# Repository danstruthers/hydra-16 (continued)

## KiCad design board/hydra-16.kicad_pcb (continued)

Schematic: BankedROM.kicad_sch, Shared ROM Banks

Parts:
C38, C39, C40, C41, C42, C43, C44, C45: 104; C_Disc_D5.0mm_W2.5mm_P5.00mm
U30, U31, U32, U33, U34, U35, U36, U37: SST39SF040; DIP-32_W15.24mm_Socket_LongPads

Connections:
!RWB: U30.24 (OE), U31.24 (OE), U32.24 (OE), U33.24 (OE), U34.24 (OE), U35.24 (OE), U36.24 (OE), U37.24 (OE); also elsewhere on the board
+5V: C38.1, C39.2, C40.2, C41.2, C42.2, C43.2, C44.2, C45.2, U30.31 (PGM), U30.32 (VCC), U31.31 (PGM), U31.32 (VCC), U32.31 (PGM), U32.32 (VCC), U33.31 (PGM), U33.32 (VCC), U34.31 (PGM), U34.32 (VCC), U35.31 (PGM), U35.32 (VCC), U36.31 (PGM), U36.32 (VCC), U37.31 (PGM), U37.32 (VCC); also elsewhere on the board
A0: U30.12 (A0), U31.12 (A0), U32.12 (A0), U33.12 (A0), U34.12 (A0), U35.12 (A0), U36.12 (A0), U37.12 (A0); also elsewhere on the board
A1: U30.11 (A1), U31.11 (A1), U32.11 (A1), U33.11 (A1), U34.11 (A1), U35.11 (A1), U36.11 (A1), U37.11 (A1); also elsewhere on the board
A2: U30.10 (A2), U31.10 (A2), U32.10 (A2), U33.10 (A2), U34.10 (A2), U35.10 (A2), U36.10 (A2), U37.10 (A2); also elsewhere on the board
A3: U30.9 (A3), U31.9 (A3), U32.9 (A3), U33.9 (A3), U34.9 (A3), U35.9 (A3), U36.9 (A3), U37.9 (A3); also elsewhere on the board
A4: U30.8 (A4), U31.8 (A4), U32.8 (A4), U33.8 (A4), U34.8 (A4), U35.8 (A4), U36.8 (A4), U37.8 (A4); also elsewhere on the board
A5: U30.7 (A5), U31.7 (A5), U32.7 (A5), U33.7 (A5), U34.7 (A5), U35.7 (A5), U36.7 (A5), U37.7 (A5); also elsewhere on the board
A6: U30.6 (A6), U31.6 (A6), U32.6 (A6), U33.6 (A6), U34.6 (A6), U35.6 (A6), U36.6 (A6), U37.6 (A6); also elsewhere on the board
A7: U30.5 (A7), U31.5 (A7), U32.5 (A7), U33.5 (A7), U34.5 (A7), U35.5 (A7), U36.5 (A7), U37.5 (A7); also elsewhere on the board
A8: U30.27 (A8), U31.27 (A8), U32.27 (A8), U33.27 (A8), U34.27 (A8), U35.27 (A8), U36.27 (A8), U37.27 (A8); also elsewhere on the board
A9: U30.26 (A9), U31.26 (A9), U32.26 (A9), U33.26 (A9), U34.26 (A9), U35.26 (A9), U36.26 (A9), U37.26 (A9); also elsewhere on the board
A10: U30.23 (A10), U31.23 (A10), U32.23 (A10), U33.23 (A10), U34.23 (A10), U35.23 (A10), U36.23 (A10), U37.23 (A10); also elsewhere on the board
A11: U30.25 (A11), U31.25 (A11), U32.25 (A11), U33.25 (A11), U34.25 (A11), U35.25 (A11), U36.25 (A11), U37.25 (A11); also elsewhere on the board
A12: U30.4 (A12), U31.4 (A12), U32.4 (A12), U33.4 (A12), U34.4 (A12), U35.4 (A12), U36.4 (A12), U37.4 (A12); also elsewhere on the board
A13: U30.28 (A13), U31.28 (A13), U32.28 (A13), U33.28 (A13), U34.28 (A13), U35.28 (A13), U36.28 (A13), U37.28 (A13); also elsewhere on the board
D0: U30.13 (D0), U31.13 (D0), U32.13 (D0), U33.13 (D0), U34.13 (D0), U35.13 (D0), U36.13 (D0), U37.13 (D0); also elsewhere on the board
D1: U30.14 (D1), U31.14 (D1), U32.14 (D1), U33.14 (D1), U34.14 (D1), U35.14 (D1), U36.14 (D1), U37.14 (D1); also elsewhere on the board
D2: U30.15 (D2), U31.15 (D2), U32.15 (D2), U33.15 (D2), U34.15 (D2), U35.15 (D2), U36.15 (D2), U37.15 (D2); also elsewhere on the board
D3: U30.17 (D3), U31.17 (D3), U32.17 (D3), U33.17 (D3), U34.17 (D3), U35.17 (D3), U36.17 (D3), U37.17 (D3); also elsewhere on the board
D4: U30.18 (D4), U31.18 (D4), U32.18 (D4), U33.18 (D4), U34.18 (D4), U35.18 (D4), U36.18 (D4), U37.18 (D4); also elsewhere on the board
D5: U30.19 (D5), U31.19 (D5), U32.19 (D5), U33.19 (D5), U34.19 (D5), U35.19 (D5), U36.19 (D5), U37.19 (D5); also elsewhere on the board
D6: U30.20 (D6), U31.20 (D6), U32.20 (D6), U33.20 (D6), U34.20 (D6), U35.20 (D6), U36.20 (D6), U37.20 (D6); also elsewhere on the board
D7: U30.21 (D7), U31.21 (D7), U32.21 (D7), U33.21 (D7), U34.21 (D7), U35.21 (D7), U36.21 (D7), U37.21 (D7); also elsewhere on the board
GND: C38.2, C39.1, C40.1, C41.1, C42.1, C43.1, C44.1, C45.1, U30.16 (GND), U31.16 (GND), U32.16 (GND), U33.16 (GND), U34.16 (GND), U35.16 (GND), U36.16 (GND), U37.16 (GND); also elsewhere on the board
ROMB0: U30.29 (A14), U31.29 (A14), U32.29 (A14), U33.29 (A14), U34.29 (A14), U35.29 (A14), U36.29 (A14), U37.29 (A14); also elsewhere on the board
ROMB1: U30.3 (A15), U31.3 (A15), U32.3 (A15), U33.3 (A15), U34.3 (A15), U35.3 (A15), U36.3 (A15), U37.3 (A15); also elsewhere on the board
ROMB2: U30.2 (A16), U31.2 (A16), U32.2 (A16), U33.2 (A16), U34.2 (A16), U35.2 (A16), U36.2 (A16), U37.2 (A16); also elsewhere on the board
ROMB3: U30.30 (A17), U31.30 (A17), U32.30 (A17), U33.30 (A17), U34.30 (A17), U35.30 (A17), U36.30 (A17), U37.30 (A17); also elsewhere on the board
ROMB4: U30.1 (A18), U31.1 (A18), U32.1 (A18), U33.1 (A18), U34.1 (A18), U35.1 (A18), U36.1 (A18), U37.1 (A18); also elsewhere on the board
nBROMC0_S: U31.22 (CE); also elsewhere on the board
nBROMC1_S: U32.22 (CE); also elsewhere on the board
nBROMC2_S: U34.22 (CE); also elsewhere on the board
nBROMC3_S: U36.22 (CE); also elsewhere on the board
nBROMC4_S: U30.22 (CE); also elsewhere on the board
nBROMC5_S: U33.22 (CE); also elsewhere on the board
nBROMC6_S: U35.22 (CE); also elsewhere on the board
nBROMC7_S: U37.22 (CE); also elsewhere on the board

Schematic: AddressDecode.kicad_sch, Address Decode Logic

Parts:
C13, C14, C15, C16, C17, C18, C20, C21, C22, C23, C24, C25, C26: 104; C_Disc_D5.0mm_W2.5mm_P5.00mm
R27: 220; R_Axial_DIN0207_L6.3mm_D2.5mm_P10.16mm_Horizontal
U8, U9: 74LS260; DIP-14_W7.62mm_Socket_LongPads
U10: 74F20; DIP-14_W7.62mm_Socket_LongPads
U11: 74ACT08; DIP-14_W7.62mm_Socket_LongPads
U12: 74F86; DIP-14_W7.62mm_Socket_LongPads
U13, U16: 74F32; DIP-14_W7.62mm_Socket_LongPads
U14: 74F30; DIP-14_W7.62mm_Socket_LongPads
U15: 74F00; DIP-14_W7.62mm_Socket_LongPads
U19: 74LS154; DIP-24_W15.24mm_Socket_LongPads
U20: 74F138; DIP-16_W7.62mm_Socket_LongPads
U21: 74F541; DIP-20_W7.62mm_Socket_LongPads
U22: 74ACT240; DIP-20_W7.62mm_Socket_LongPads

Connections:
!A0: U22.7 (O1b); also elsewhere on the board
!A3: U12.1, U22.3 (O3b)
!RWB: U10.1, U11.5, U22.18 (O0a); also elsewhere on the board
+5V: C13.2, C14.2, C15.2, C16.2, C17.2, C18.2, C20.2, C21.2, C22.2, C23.2, C24.1, C25.1, C26.2, U8.14 (VCC), U9.14 (VCC), U10.14 (VCC), U11.14 (VCC), U12.4, U12.5, U12.14 (VCC), U13.14 (VCC), U14.14 (VCC), U15.12, U15.13, U15.14 (VCC), U16.14 (VCC), U19.24 (VCC), U20.16 (VCC), U21.20 (VCC), U22.20 (VCC); also elsewhere on the board
A0: U20.1 (A0), U22.13 (I1b); also elsewhere on the board
A1: U8.9, U12.13, U20.2 (A1); also elsewhere on the board
A2: U8.8, U12.2, U12.12, U20.3 (A2); also elsewhere on the board
A3: U8.13, U15.9, U22.17 (I3b); also elsewhere on the board
A4: U8.12, U19.23 (A0); also elsewhere on the board
A5: U8.3, U19.22 (A1); also elsewhere on the board
A6: U8.2, U19.21 (A2); also elsewhere on the board
A7: U8.1, U19.20 (A3); also elsewhere on the board
A8: U9.13, U14.12; also elsewhere on the board
A9: U9.12, U14.11; also elsewhere on the board
A10: U9.3, U14.6; also elsewhere on the board
A11: U9.2, U14.5; also elsewhere on the board
A12: U9.1, U14.4; also elsewhere on the board
A13: U8.4, U9.8, U10.12, U12.10, U14.3; also elsewhere on the board
A14: U8.11, U9.9, U10.10, U12.9, U14.2; also elsewhere on the board
A15: U8.10, U10.9, U11.12, U14.1; also elsewhere on the board
DDIR_S: U11.6; also elsewhere on the board
DMA: U22.16 (O1a); also elsewhere on the board
DMAB: U11.1, U22.4 (I1a); also elsewhere on the board
GND: C13.1, C14.1, C15.1, C16.1, C17.1, C18.1, C20.1, C21.1, C22.1, C23.1, C24.2, C25.2, C26.1, U8.7 (GND), U9.4, U9.7 (GND), U9.10, U9.11, U10.7 (GND), U11.7 (GND), U12.7 (GND), U13.7 (GND), U14.7 (GND), U15.7 (GND), U16.7 (GND), U19.12 (GND), U19.19 (~E1), U20.8 (GND), U21.1 (G1), U21.10 (GND), U21.19 (G2), U22.1 (OEa), U22.10 (GND), U22.11 (I0b), U22.15 (I2b), U22.19 (OEb); also elsewhere on the board
IRQ: U22.8 (I3a); also elsewhere on the board
IRQB: U22.12 (O3a); also elsewhere on the board
unnamed: U8.5, U10.2
unnamed: U8.6, U10.4
unnamed: U9.5, U10.5
unnamed: U10.6, U16.1
unnamed: U10.8, U11.9
unnamed: U11.8, U16.10
unnamed: U11.11, U15.2, U15.4
unnamed: U12.8, U15.1
unnamed: U12.11, U15.10
unnamed: U13.13, U15.8
unnamed: U9.6, U15.5
unnamed: U12.3, U20.6 (E2)
PHI1: R27.2, U13.2, U16.2, U16.9; also elsewhere on the board
PHI1_SRC: R27.1, U22.14 (O2a)
PHI2: U11.2, U11.4, U11.13, U22.6 (I2a); also elsewhere on the board
P_PHI0: U11.3; also elsewhere on the board
RAMB0: U21.6 (A4); also elsewhere on the board
RAMB1: U21.7 (A5); also elsewhere on the board
RAMB2: U21.8 (A6); also elsewhere on the board
RAMB3: U21.9 (A7); also elsewhere on the board
RAMB_M0: U21.14 (Y4); also elsewhere on the board
RAMB_M1: U21.13 (Y5); also elsewhere on the board
RAMB_M2: U21.12 (Y6); also elsewhere on the board
RAMB_M3: U21.11 (Y7); also elsewhere on the board
RWB: U22.2 (I0a); also elsewhere on the board
T0: U21.2 (A0); also elsewhere on the board
T1: U21.3 (A1); also elsewhere on the board
T2: U21.4 (A2); also elsewhere on the board
T3: U21.5 (A3); also elsewhere on the board
T_M0: U21.18 (Y0); also elsewhere on the board
T_M1: U21.17 (Y1); also elsewhere on the board
T_M2: U21.16 (Y2); also elsewhere on the board
T_M3: U21.15 (Y3); also elsewhere on the board
nBRA_S: U15.6; also elsewhere on the board
nBRO_S: U15.3; also elsewhere on the board
nFFFE_S: U13.6; also elsewhere on the board
nFFFF_S: U13.8; also elsewhere on the board
nFFxx_S: U10.13, U13.1, U14.8
nIOB0_S: U20.15 (~Y0); also elsewhere on the board
nIOB1_S: U20.14 (~Y1); also elsewhere on the board
nIOB2_S: U20.13 (~Y2); also elsewhere on the board
nIOB3_S: U20.12 (~Y3); also elsewhere on the board
nIOB12_S: U20.11 (~Y4)
nIOB13_S: U20.10 (~Y5)
nIOB14_S: U13.5, U20.9 (~Y6)
nIOB15_S: U13.10, U20.7 (~Y7)
nIOP0_S: U19.1 (~S0); also elsewhere on the board
nIOP1_S: U19.2 (~S1); also elsewhere on the board
nIOP2_S: U19.3 (~S2); also elsewhere on the board
nIOP3_S: U19.4 (~S3); also elsewhere on the board
nIOP4_S: U19.5 (~S4); also elsewhere on the board
nIOP5_S: U19.6 (~S5); also elsewhere on the board
nIOP6_S: U19.7 (~S6); also elsewhere on the board
nIOP7_S: U19.8 (~S7); also elsewhere on the board
nIOP8_S: U19.9 (~S8); also elsewhere on the board
nIOP9_S: U19.10 (~S9); also elsewhere on the board
nIOP10_S: U19.11 (~S10); also elsewhere on the board
nIOP11_S: U19.13 (~S11); also elsewhere on the board
nIOP12_S: U19.14 (~S12); also elsewhere on the board
nIOP13_S: U19.15 (~S13); also elsewhere on the board
nIOP14_S: U19.16 (~S14); also elsewhere on the board
nIOP15_S: U13.4, U13.9, U13.12, U19.17 (~S15), U20.5 (~E1); also elsewhere on the board
nIO_S: U13.3, U19.18 (~E0), U20.4 (~E0); also elsewhere on the board
nOSRV_S: U11.10, U13.11
nOSR_S: U16.8; also elsewhere on the board
nZPR_W: U16.3; also elsewhere on the board

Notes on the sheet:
1.8D: U11 and U22 are 74ACT (CMOS highs on the CPU's clock and IRQB); U22's spare inputs tied low; R27, 22 ohms in PHI1

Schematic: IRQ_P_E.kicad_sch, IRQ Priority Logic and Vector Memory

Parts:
C19, C57, C58, C59, C60, C61, C62, C63: 104; C_Disc_D5.0mm_W2.5mm_P5.00mm
IC5, IC6, IC7, IC8: 74LS219; DIP-16_W7.62mm_Socket_LongPads; Manufacturer_Part_Number SN74LS219AN
RN2, RN3: 332; R_Array_SIP9
U17, U18: 74LS148; DIP-16_W7.62mm_Socket_LongPads
U44: 74F00; DIP-14_W7.62mm_Socket_LongPads
U45: 74F157; DIP-16_W7.62mm_Socket_LongPads

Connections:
+5V: C19.1, C57.1, C58.1, C59.1, C60.1, C61.1, C62.1, C63.1, IC5.16 (VCC), IC6.16 (VCC), IC7.16 (VCC), IC8.16 (VCC), RN2.1 (common), RN3.1 (common), U17.16 (VCC), U18.16 (VCC), U44.14 (VCC), U45.16 (VCC); also elsewhere on the board
D0: IC5.4 (D1), IC5.5 (Q1), IC7.4 (D1), IC7.5 (Q1); also elsewhere on the board
D1: IC5.6 (D2), IC5.7 (Q2), IC7.6 (D2), IC7.7 (Q2); also elsewhere on the board
D2: IC5.9 (Q3), IC5.10 (D3), IC7.9 (Q3), IC7.10 (D3); also elsewhere on the board
D3: IC5.11 (Q4), IC5.12 (D4), IC7.11 (Q4), IC7.12 (D4); also elsewhere on the board
D4: IC6.4 (D1), IC6.5 (Q1), IC8.4 (D1), IC8.5 (Q1); also elsewhere on the board
D5: IC6.6 (D2), IC6.7 (Q2), IC8.6 (D2), IC8.7 (Q2); also elsewhere on the board
D6: IC6.11 (Q4), IC6.12 (D4), IC8.11 (Q4), IC8.12 (D4); also elsewhere on the board
D7: IC6.9 (Q3), IC6.10 (D3), IC8.9 (Q3), IC8.10 (D3); also elsewhere on the board
GND: C19.2, C57.2, C58.2, C59.2, C60.2, C61.2, C62.2, C63.2, IC5.8 (GND), IC6.8 (GND), IC7.8 (GND), IC8.8 (GND), U17.5 (~EI), U17.8 (GND), U18.8 (GND), U44.7 (GND), U45.8 (GND), U45.15 (~EN); also elsewhere on the board
IRQ: U44.3, U45.1 (A/B); also elsewhere on the board
unnamed: U17.15 (~EO), U18.5 (~EI)
unnamed: U17.14 (~GS), U44.2, U45.10 (I1d)
unnamed: U17.9 (~S0), U44.5
unnamed: U17.7 (~S1), U44.10
unnamed: U17.6 (~S2), U44.13
unnamed: U18.14 (~GS), U44.1
unnamed: U18.9 (~S0), U44.4
unnamed: U18.7 (~S1), U44.9
unnamed: U18.6 (~S2), U44.12
unnamed: U44.6, U45.3 (I1a)
unnamed: U44.8, U45.6 (I1b)
unnamed: U44.11, U45.13 (I1c)
RWB: IC5.3 (R/~W), IC6.3 (R/~W), IC7.3 (R/~W), IC8.3 (R/~W); also elsewhere on the board
V0: U45.2 (I0a); also elsewhere on the board
V1: U45.5 (I0b); also elsewhere on the board
V2: U45.14 (I0c); also elsewhere on the board
V3: U45.11 (I0d); also elsewhere on the board
nFFFE_S: IC5.2 (~S), IC6.2 (~S); also elsewhere on the board
nFFFF_S: IC7.2 (~S), IC8.2 (~S); also elsewhere on the board
nIRQ0: RN2.5 (R4), U17.4 (~I7); also elsewhere on the board
nIRQ1: RN2.4 (R3), U17.3 (~I6); also elsewhere on the board
nIRQ2: RN2.3 (R2), U17.2 (~I5); also elsewhere on the board
nIRQ3: RN2.2 (R1), U17.1 (~I4); also elsewhere on the board
nIRQ4: RN2.6 (R5), U17.13 (~I3); also elsewhere on the board
nIRQ5: RN2.7 (R6), U17.12 (~I2); also elsewhere on the board
nIRQ6: RN2.8 (R7), U17.11 (~I1); also elsewhere on the board
nIRQ7: RN2.9 (R8), U17.10 (~IO); also elsewhere on the board
nIRQ8: RN3.5 (R4), U18.4 (~I7); also elsewhere on the board
nIRQ9: RN3.4 (R3), U18.3 (~I6); also elsewhere on the board
nIRQ10: RN3.3 (R2), U18.2 (~I5); also elsewhere on the board
nIRQ11: RN3.2 (R1), U18.1 (~I4); also elsewhere on the board
nIRQ12: RN3.6 (R5), U18.13 (~I3); also elsewhere on the board
nIRQ13: RN3.7 (R6), U18.12 (~I2); also elsewhere on the board
nIRQ14: RN3.8 (R7), U18.11 (~I1); also elsewhere on the board
nIRQ15: RN3.9 (R8), U18.10 (~IO)
q0: IC5.1 (A0), IC6.1 (A0), IC7.1 (A0), IC8.1 (A0), U45.4 (Qa)
q1: IC5.15 (A1), IC6.15 (A1), IC7.15 (A1), IC8.15 (A1), U45.7 (Qb)
q2: IC5.14 (A2), IC6.14 (A2), IC7.14 (A2), IC8.14 (A2), U45.12 (Qc)
q3: IC5.13 (A3), IC6.13 (A3), IC7.13 (A3), IC8.13 (A3), U45.9 (Qd)

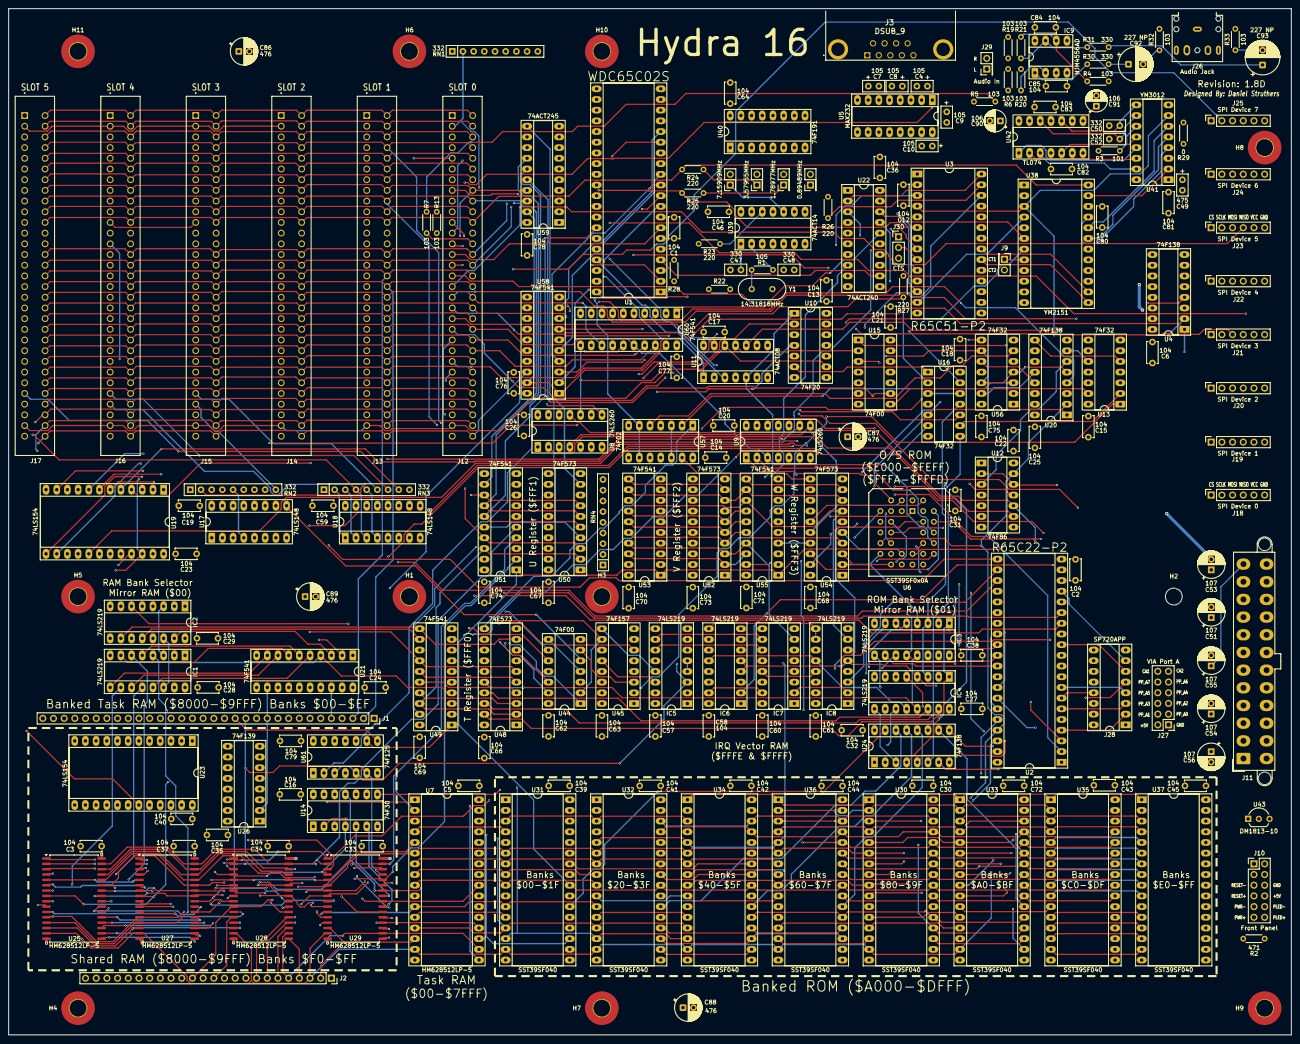
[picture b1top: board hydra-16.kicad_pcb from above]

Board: 6 copper layers, 304.8 x 243.8 mm, 227 parts (0 on the bottom side), 336 nets.

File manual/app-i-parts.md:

# Appendix I. Parts and Board Diagrams

This appendix lists every part of the Hydra-16 (board revision 1.8D) and its memory cards, in the order Chapter 4
fits them, with a box to tick as each one goes in. Then it says what each chip does, and shows where every part is.

## I.1 The main board's parts

**Resistors** (Chapter 4, step 2):

| ☐ | Parts | Value | Code |
|---|---|---|---|
| ☐ | R23, R24, R25, R26, R27 | 22 Ω | 220 |
| ☐ | R30, R31 | 33 Ω | 330 |
| ☐ | R3 | 100 Ω | 101 |
| ☐ | R22 | 330 Ω | 331 |
| ☐ | R2 | 470 Ω | 471 |
| ☐ | R4, R5, R6, R7, R13, R19, R20, R21, R28, R32, R33 | 10 kΩ | 103 |
| ☐ | R1 | 1 MΩ | 105 |
| ☐ | R29 | 0 Ω (a link) | 0 |
| ☐ | RN1, RN2, RN3 (networks of 8, 9 pins) | 3.3 kΩ | 332 |
| ☐ | RN4 (a network of 8, 9 pins) | 10 kΩ | 103 |

**Ceramic capacitors** (step 3):

| ☐ | Parts | Value | Code |
|---|---|---|---|
| ☐ | C47, C48 | 33 pF | 330 |
| ☐ | C50, C52 | 3.3 nF | 332 |
| ☐ | C1, C2, C3, C5, C6, C12 to C46, C57 to C64, C66 to C85 (68) | 100 nF | 104 |
| ☐ | C4, C7, C8, C9, C10 | 1 µF | 105 |
| ☐ | C49 | 4.7 µF | 475 |

**Sockets** (step 4), and the chips that go in them (section 4.5):

| ☐ | Place | Socket | Chip |
|---|---|---|---|
| ☐ | U1 | 40 pins, wide | W65C02S |
| ☐ | U2 | 40 pins, wide | R65C22 (or a W65C22N) |
| ☐ | U3 | 28 pins, wide | R65C51 (or a W65C51N: section 4.5) |
| ☐ | U4, U20, U24 | 16 pins | 74F138 |
| ☐ | U5 | 16 pins | MAX232 |
| ☐ | U6 | PLCC-32 | SST39SF010A |
| ☐ | U7 | 32 pins, wide | HM628512LP-5 (or a DS1747) |
| ☐ | U8, U9 | 14 pins | 74LS260 |
| ☐ | U10 | 14 pins | 74F20 |
| ☐ | U11 | 14 pins | 74ACT08 |
| ☐ | U12 | 14 pins | 74F86 |
| ☐ | U13, U16, U56 | 14 pins | 74F32 |
| ☐ | U14 | 14 pins | 74F30 |
| ☐ | U15, U44 | 14 pins | 74F00 |
| ☐ | U17, U18 | 16 pins | 74LS148 |
| ☐ | U19, U23 | 24 pins, wide | 74LS154 |
| ☐ | U21, U49, U51, U53, U55, U58, U60 | 20 pins | 74F541 |
| ☐ | U22 | 20 pins | 74ACT240 |
| ☐ | U26 | 16 pins | 74F139 |
| ☐ | U30 to U37 | 32 pins, wide | SST39SF040 (U31, U32 and U34 programmed; the rest empty) |
| ☐ | U38 | 24 pins, wide | YM2151 |
| ☐ | U39 | 14 pins | 74ACT14 |
| ☐ | U40 | 16 pins | 74F191 |
| ☐ | U41 | 16 pins | YM3012 |
| ☐ | U42 | 14 pins | TL074 |
| ☐ | U45 | 16 pins | 74F157 |
| ☐ | U48, U50, U52, U54 | 20 pins | 74F573 |
| ☐ | U57 | 14 pins | 74F02 |
| ☐ | U59 | 20 pins | 74ACT245 |
| ☐ | U61 | 14 pins | 74F125 |
| ☐ | IC1 to IC8 | 16 pins | 74LS219 |
| ☐ | IC9 | 8 pins | NJM4556AD |
| ☐ | J28 | 16 pins | SP720 |

**Soldered straight to the board** (steps 1, 5, 6 and 7):

| ☐ | Parts | What |
|---|---|---|
| ☐ | U25, U27, U28, U29 | HM628512 RAM chips, surface-mount (SOP-32) |
| ☐ | Y1 | 14.31818 MHz crystal |
| ☐ | U43 | DS1813-10 reset chip (TO-92) |
| ☐ | J5, J6, J7, J8 | 2-pin headers: the clock jumpers (0.89, 1.79, 3.58 and 7.16 MHz) |
| ☐ | J9, J29 | 2-pin headers: the sound chip's CT1/CT2, and Audio In |
| ☐ | J30 | 3-pin header: the serial port's CTS |
| ☐ | J10 | 2 × 6 header: the front panel |
| ☐ | J27 | 2 × 6 header: the I/O header (the VIA's port A) |
| ☐ | J18 to J25 | 6-hole pin sockets: SPI devices 0 to 7 |
| ☐ | J1, J2 | 32-hole and 24-hole pin sockets: the memory card |
| ☐ | C90, C91 | 10 µF electrolytic (106) |
| ☐ | C86, C87, C88, C89 | 47 µF electrolytic (476) |
| ☐ | C51, C53, C54, C55, C56 | 100 µF electrolytic (107) |
| ☐ | C92, C93 | 220 µF non-polarized electrolytic (227 NP) |
| ☐ | J3 | 9-pin D socket (female): the serial port |
| ☐ | J26 | 3.5 mm stereo audio jack |
| ☐ | J12 to J17 | 62-pin card edge connectors: slots 0 to 5 |
| ☐ | J11 | 24-pin ATX power connector |

**Jumpers** (section 4.6): one on J7 (the clock), one on J30 (pins 1 and 2), and one for each RAM module (section
4.7). J9 and J29 get none.

## I.2 What each chip does

| Chips | Part | Its job |
|---|---|---|
| U1 | W65C02S | The processor (Chapter 26) |
| U2 | 65C22 VIA | The tick (its timer), the SPI bus, and the I/O header J27 |
| U3 | 65C51 ACIA | The serial port |
| U5 | MAX232 | Turns the ACIA's 5-volt signals into the serial cable's RS-232 ones, and back |
| U6 | SST39SF010A | The kernel ROM: 16 pages of 8K |
| U7 | HM628512 | The task RAM: 512K, 32K for each of the 16 tasks |
| U25, U27, U28, U29 | HM628512 | The shared RAM: 2 MB |
| U26 | 74F139 | Chooses one of the shared RAM chips |
| U30 to U37 | SST39SF040 | The paged ROM: up to 4 MB |
| U4, U8 to U16, U19 to U22 | 74-series logic | The **address decoder**: works out, from each address, which chip answers |
| U48, U50, U52, U54 | 74F573 | The registers T, U, V and W |
| U49, U51, U53, U55 | 74F541 | Read T, U, V and W back |
| U56, U57 | 74F32, 74F02 | Gates that tell the registers when they're written and read |
| IC1 to IC4, U23, U24 | 74LS219, 74LS154, 74F138 | The bank registers: a RAM and a ROM bank register for every task |
| U17, U18, U44, U45 | 74LS148, 74F00, 74F157 | The interrupts' priority encoder |
| IC5 to IC8 | 74LS219 | The vector RAM: an interrupt handler's address for each line |
| U58, U59, U60, U61 | 74F541, 74ACT245, 74F125 | The slots' buffers: they drive the address, data and control lines to the six slots |
| Y1, U39, U40 | Crystal, 74ACT14, 74F191 | The clock: the crystal's 14.31818 MHz, divided by 4 (or 16, 8 or 2) for the processor |
| U43 | DS1813 | The reset: holds the processor in reset at power-up, and when RESET is pressed |
| U38 | YM2151 | The FM sound chip |
| U41 | YM3012 | Turns the YM2151's sound into a voltage |
| U42, IC9 | TL074, NJM4556 | The sound's mixer and headphone amplifier |
| J28 | SP720 | Protects the I/O header's pins from static |

## I.3 The memory cards

The through-hole card (Figure 4-8):

| ☐ | Parts | What |
|---|---|---|
| ☐ | C1 to C5 | 100 nF ceramic capacitors (104) |
| ☐ | U1 | 74LS139 (a 16-pin socket) |
| ☐ | IC1 to IC4 | HM628512LP-7 RAM chips, in 32-pin wide sockets: one RAM module |
| ☐ | J1, J2 | 32-pin and 24-pin headers, under the card: they plug into the main board |
| ☐ | J3 | 2 × 15 header: the module number's jumper (section 4.7) |

The surface-mount card (Figure 4-10):

| ☐ | Parts | What |
|---|---|---|
| ☐ | C1 to C5 | 100 nF ceramic capacitors (104) |
| ☐ | U1 | 74LS139 |
| ☐ | IC1 to IC8 | HM628512LFP-7 RAM chips, surface-mount: two RAM modules |
| ☐ | J1, J2 | 32-pin and 24-pin headers, under the card |
| ☐ | J3 | 2 × 15 header: the first module's number (IC1 to IC4) |
| ☐ | J4 | 15-pin header: with J3, the second module's number (IC5 to IC8) |

## I.4 The board

<figure>
<img src="figures/board-parts.svg" alt="The Hydra-16's circuit board, every part named, coloured by kind">
<figcaption>Figure I-1. Every part of the main board, by kind.</figcaption>
</figure>

Figure 1-1 shows the board by what its parts do, and Figures 4-1 to 4-7 each step of building it.

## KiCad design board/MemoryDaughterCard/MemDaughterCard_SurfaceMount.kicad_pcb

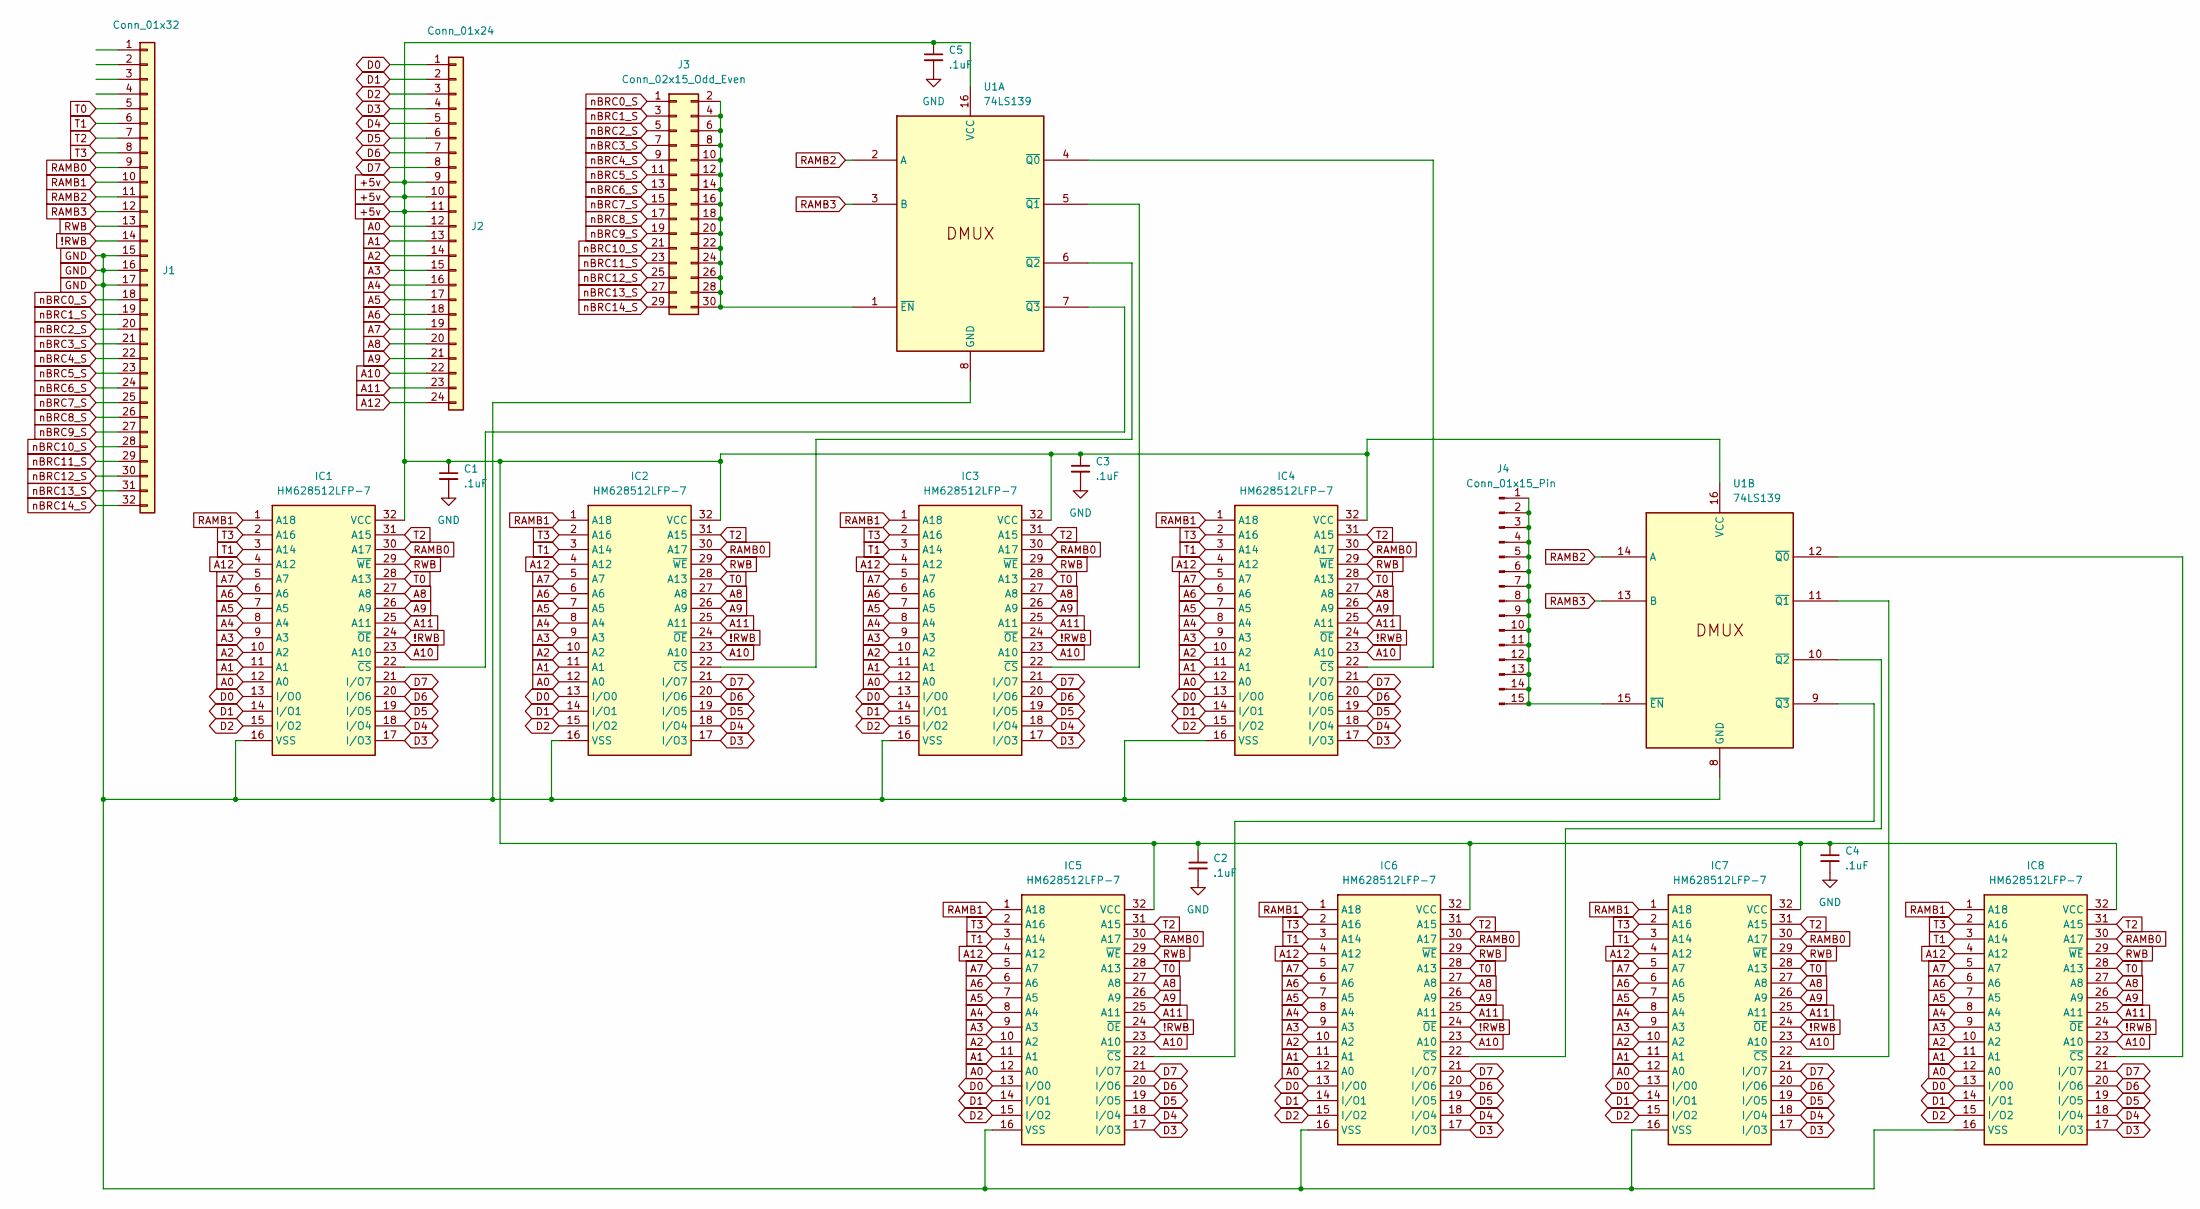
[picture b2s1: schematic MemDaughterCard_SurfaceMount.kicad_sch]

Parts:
C1, C2, C3, C4, C5: .1uF; C_Disc_D5.0mm_W2.5mm_P5.00mm
IC1, IC2, IC3, IC4, IC5, IC6, IC7, IC8: HM628512LFP-7; SOIC127P1414X300-32N; Manufacturer_Part_Number HM628512LFP-7
J1: Conn_01x32; PinHeader_1x32_P2.54mm_Vertical
J2: Conn_01x24; PinHeader_1x24_P2.54mm_Vertical
J3: Conn_02x15_Odd_Even; PinHeader_2x15_P2.54mm_Vertical
J4: Conn_01x15_Pin; PinHeader_1x15_P2.54mm_Vertical
U1: 74LS139; DIP-16_W7.62mm

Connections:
!RWB: IC1.24 (~OE), IC2.24 (~OE), IC3.24 (~OE), IC4.24 (~OE), IC5.24 (~OE), IC6.24 (~OE), IC7.24 (~OE), IC8.24 (~OE), J1.14
+5v: C1.1, C2.1, C3.1, C4.1, C5.1, IC1.32 (VCC), IC2.32 (VCC), IC3.32 (VCC), IC4.32 (VCC), IC5.32 (VCC), IC6.32 (VCC), IC7.32 (VCC), IC8.32 (VCC), J2.9, J2.10, J2.11, U1.16 (VCC)
A0: IC1.12 (A0), IC2.12 (A0), IC3.12 (A0), IC4.12 (A0), IC5.12 (A0), IC6.12 (A0), IC7.12 (A0), IC8.12 (A0), J2.12
A1: IC1.11 (A1), IC2.11 (A1), IC3.11 (A1), IC4.11 (A1), IC5.11 (A1), IC6.11 (A1), IC7.11 (A1), IC8.11 (A1), J2.13
A2: IC1.10 (A2), IC2.10 (A2), IC3.10 (A2), IC4.10 (A2), IC5.10 (A2), IC6.10 (A2), IC7.10 (A2), IC8.10 (A2), J2.14
A3: IC1.9 (A3), IC2.9 (A3), IC3.9 (A3), IC4.9 (A3), IC5.9 (A3), IC6.9 (A3), IC7.9 (A3), IC8.9 (A3), J2.15
A4: IC1.8 (A4), IC2.8 (A4), IC3.8 (A4), IC4.8 (A4), IC5.8 (A4), IC6.8 (A4), IC7.8 (A4), IC8.8 (A4), J2.16
A5: IC1.7 (A5), IC2.7 (A5), IC3.7 (A5), IC4.7 (A5), IC5.7 (A5), IC6.7 (A5), IC7.7 (A5), IC8.7 (A5), J2.17
A6: IC1.6 (A6), IC2.6 (A6), IC3.6 (A6), IC4.6 (A6), IC5.6 (A6), IC6.6 (A6), IC7.6 (A6), IC8.6 (A6), J2.18
A7: IC1.5 (A7), IC2.5 (A7), IC3.5 (A7), IC4.5 (A7), IC5.5 (A7), IC6.5 (A7), IC7.5 (A7), IC8.5 (A7), J2.19
A8: IC1.27 (A8), IC2.27 (A8), IC3.27 (A8), IC4.27 (A8), IC5.27 (A8), IC6.27 (A8), IC7.27 (A8), IC8.27 (A8), J2.20
A9: IC1.26 (A9), IC2.26 (A9), IC3.26 (A9), IC4.26 (A9), IC5.26 (A9), IC6.26 (A9), IC7.26 (A9), IC8.26 (A9), J2.21
A10: IC1.23 (A10), IC2.23 (A10), IC3.23 (A10), IC4.23 (A10), IC5.23 (A10), IC6.23 (A10), IC7.23 (A10), IC8.23 (A10), J2.22
A11: IC1.25 (A11), IC2.25 (A11), IC3.25 (A11), IC4.25 (A11), IC5.25 (A11), IC6.25 (A11), IC7.25 (A11), IC8.25 (A11), J2.23
A12: IC1.4 (A12), IC2.4 (A12), IC3.4 (A12), IC4.4 (A12), IC5.4 (A12), IC6.4 (A12), IC7.4 (A12), IC8.4 (A12), J2.24
D0: IC1.13 (I/O0), IC2.13 (I/O0), IC3.13 (I/O0), IC4.13 (I/O0), IC5.13 (I/O0), IC6.13 (I/O0), IC7.13 (I/O0), IC8.13 (I/O0), J2.1
D1: IC1.14 (I/O1), IC2.14 (I/O1), IC3.14 (I/O1), IC4.14 (I/O1), IC5.14 (I/O1), IC6.14 (I/O1), IC7.14 (I/O1), IC8.14 (I/O1), J2.2
D2: IC1.15 (I/O2), IC2.15 (I/O2), IC3.15 (I/O2), IC4.15 (I/O2), IC5.15 (I/O2), IC6.15 (I/O2), IC7.15 (I/O2), IC8.15 (I/O2), J2.3
D3: IC1.17 (I/O3), IC2.17 (I/O3), IC3.17 (I/O3), IC4.17 (I/O3), IC5.17 (I/O3), IC6.17 (I/O3), IC7.17 (I/O3), IC8.17 (I/O3), J2.4
D4: IC1.18 (I/O4), IC2.18 (I/O4), IC3.18 (I/O4), IC4.18 (I/O4), IC5.18 (I/O4), IC6.18 (I/O4), IC7.18 (I/O4), IC8.18 (I/O4), J2.5
D5: IC1.19 (I/O5), IC2.19 (I/O5), IC3.19 (I/O5), IC4.19 (I/O5), IC5.19 (I/O5), IC6.19 (I/O5), IC7.19 (I/O5), IC8.19 (I/O5), J2.6
D6: IC1.20 (I/O6), IC2.20 (I/O6), IC3.20 (I/O6), IC4.20 (I/O6), IC5.20 (I/O6), IC6.20 (I/O6), IC7.20 (I/O6), IC8.20 (I/O6), J2.7
D7: IC1.21 (I/O7), IC2.21 (I/O7), IC3.21 (I/O7), IC4.21 (I/O7), IC5.21 (I/O7), IC6.21 (I/O7), IC7.21 (I/O7), IC8.21 (I/O7), J2.8
GND: C1.2, C2.2, C3.2, C4.2, C5.2, IC1.16 (VSS), IC2.16 (VSS), IC3.16 (VSS), IC4.16 (VSS), IC5.16 (VSS), IC6.16 (VSS), IC7.16 (VSS), IC8.16 (VSS), J1.15, J1.16, J1.17, U1.8 (GND)
unnamed: IC1.22 (~CS), U1.7 (~Q3)
unnamed: IC2.22 (~CS), U1.6 (~Q2)
unnamed: IC3.22 (~CS), U1.5 (~Q1)
unnamed: IC4.22 (~CS), U1.4 (~Q0)
unnamed: IC5.22 (~CS), U1.9 (~Q3)
unnamed: IC6.22 (~CS), U1.10 (~Q2)
unnamed: IC7.22 (~CS), U1.11 (~Q1)
unnamed: IC8.22 (~CS), U1.12 (~Q0)
unnamed: J3.2, J3.4, J3.6, J3.8, J3.10, J3.12, J3.14, J3.16, J3.18, J3.20, J3.22, J3.24, J3.26, J3.28, J3.30, U1.1 (~EN)
unnamed: J4.1, J4.2, J4.3, J4.4, J4.5, J4.6, J4.7, J4.8, J4.9, J4.10, J4.11, J4.12, J4.13, J4.14, J4.15, U1.15 (~EN)
RAMB0: IC1.30 (A17), IC2.30 (A17), IC3.30 (A17), IC4.30 (A17), IC5.30 (A17), IC6.30 (A17), IC7.30 (A17), IC8.30 (A17), J1.9
RAMB1: IC1.1 (A18), IC2.1 (A18), IC3.1 (A18), IC4.1 (A18), IC5.1 (A18), IC6.1 (A18), IC7.1 (A18), IC8.1 (A18), J1.10
RAMB2: J1.11, U1.2 (A), U1.14 (A)
RAMB3: J1.12, U1.3 (B), U1.13 (B)
RWB: IC1.29 (~WE), IC2.29 (~WE), IC3.29 (~WE), IC4.29 (~WE), IC5.29 (~WE), IC6.29 (~WE), IC7.29 (~WE), IC8.29 (~WE), J1.13
T0: IC1.28 (A13), IC2.28 (A13), IC3.28 (A13), IC4.28 (A13), IC5.28 (A13), IC6.28 (A13), IC7.28 (A13), IC8.28 (A13), J1.5
T1: IC1.3 (A14), IC2.3 (A14), IC3.3 (A14), IC4.3 (A14), IC5.3 (A14), IC6.3 (A14), IC7.3 (A14), IC8.3 (A14), J1.6
T2: IC1.31 (A15), IC2.31 (A15), IC3.31 (A15), IC4.31 (A15), IC5.31 (A15), IC6.31 (A15), IC7.31 (A15), IC8.31 (A15), J1.7
T3: IC1.2 (A16), IC2.2 (A16), IC3.2 (A16), IC4.2 (A16), IC5.2 (A16), IC6.2 (A16), IC7.2 (A16), IC8.2 (A16), J1.8
nBRC0_S: J1.18, J3.1
nBRC1_S: J1.19, J3.3
nBRC2_S: J1.20, J3.5
nBRC3_S: J1.21, J3.7
nBRC4_S: J1.22, J3.9
nBRC5_S: J1.23, J3.11
nBRC6_S: J1.24, J3.13
nBRC7_S: J1.25, J3.15
nBRC8_S: J1.26, J3.17
nBRC9_S: J1.27, J3.19
nBRC10_S: J1.28, J3.21
nBRC11_S: J1.29, J3.23
nBRC12_S: J1.30, J3.25
nBRC13_S: J1.31, J3.27
nBRC14_S: J1.32, J3.29

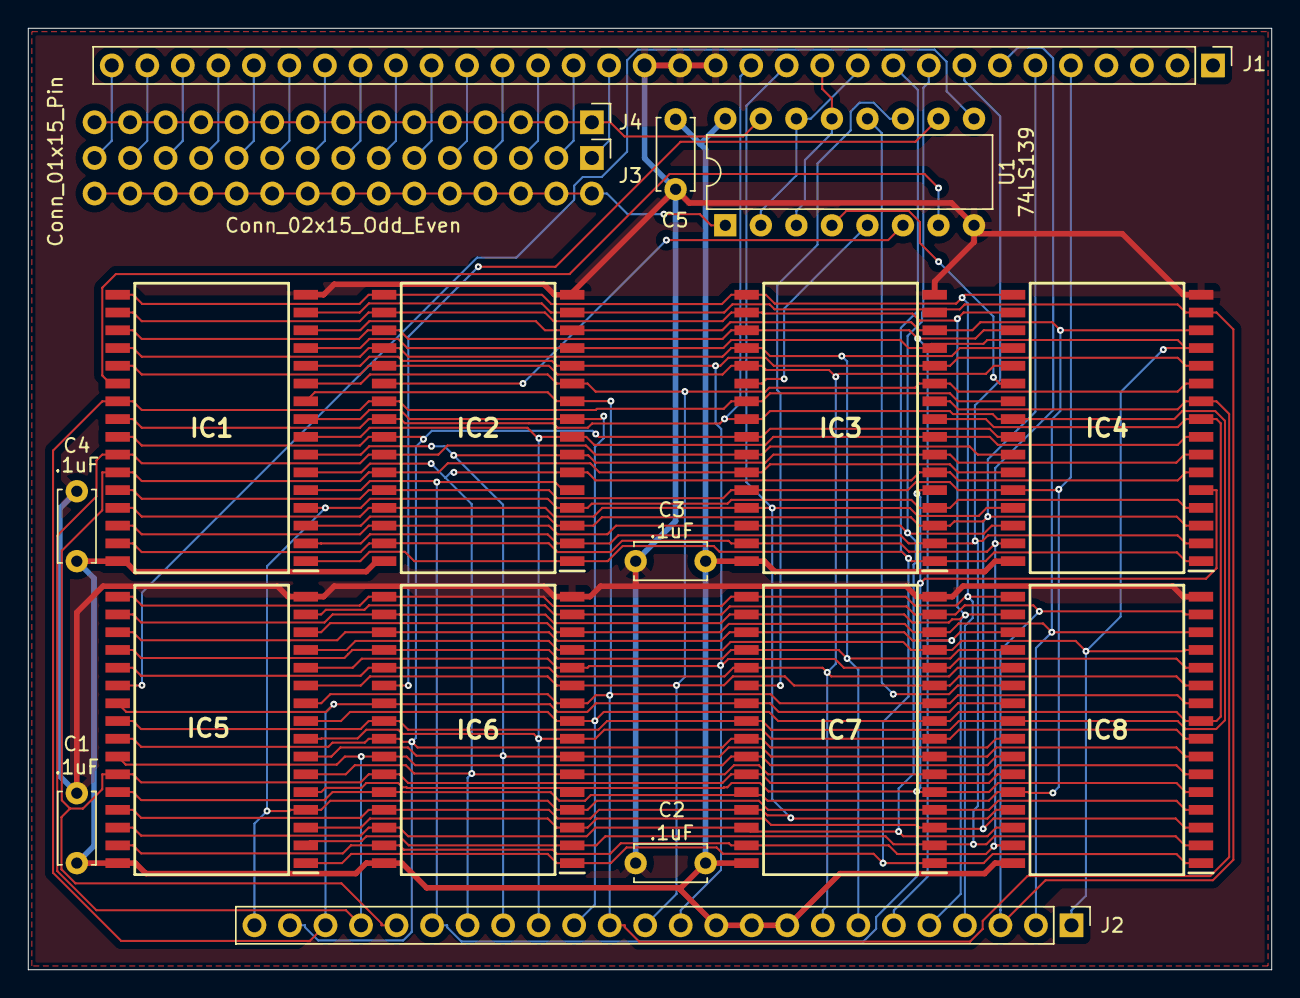
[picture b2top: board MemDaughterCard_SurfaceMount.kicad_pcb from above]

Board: 2 copper layers, 88.9 x 67.3 mm, 18 parts (0 on the bottom side), 58 nets.
